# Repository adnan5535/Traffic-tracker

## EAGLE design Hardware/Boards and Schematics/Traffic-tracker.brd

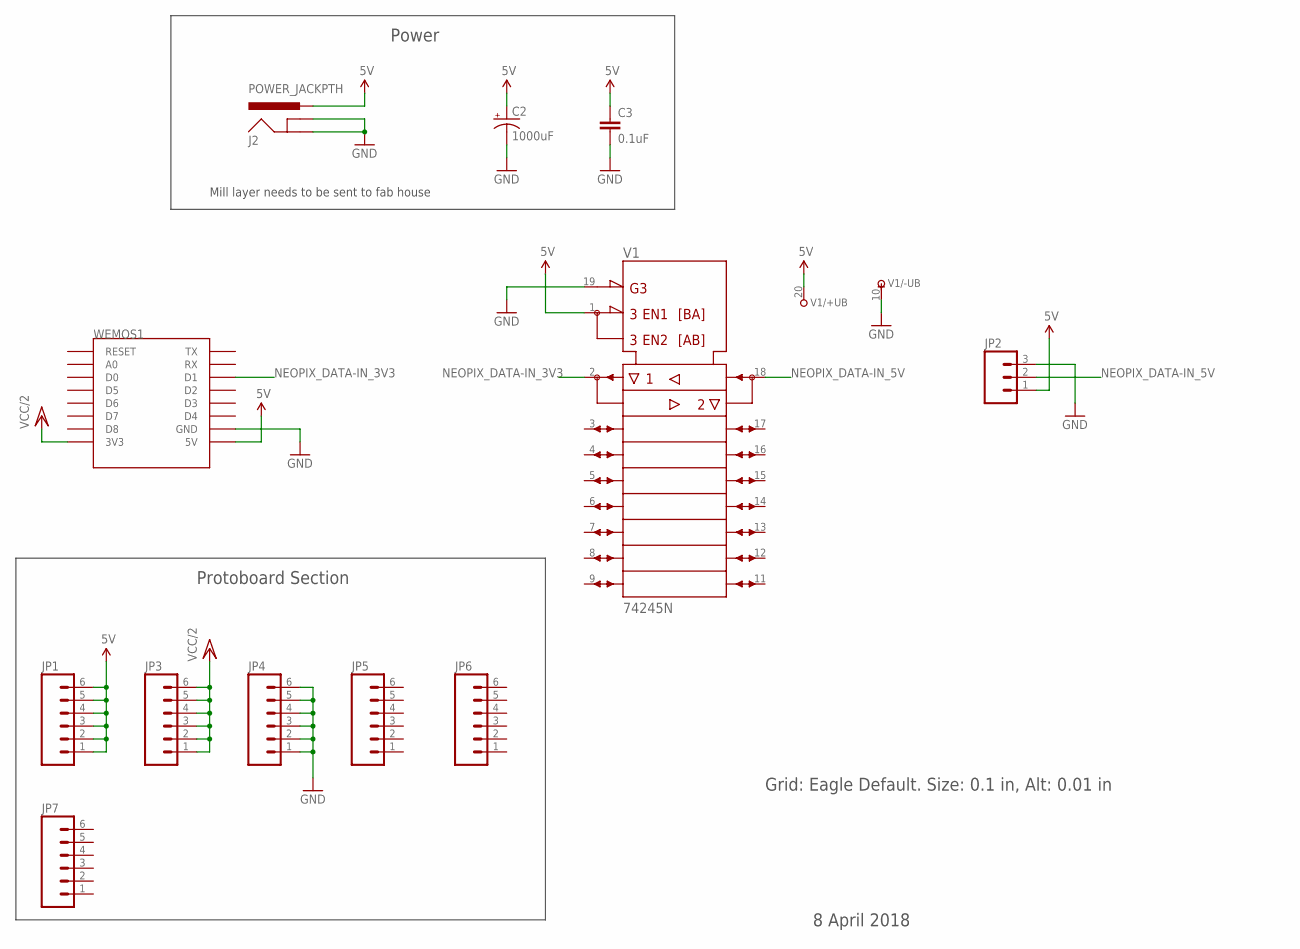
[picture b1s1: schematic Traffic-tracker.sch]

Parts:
C2: 1000uF; CPOL-RADIAL-1000UF-25V
C3: 0.1uF; 0603-CAP
J2: POWER_JACKPTH; POWER_JACK_PTH
JP1, JP3, JP4, JP5, JP6, JP7: M06POGOPIN_HOLES_ONLY; 1X06_HOLES_ONLY
JP2: M03-SCREW-5MM; SCREWTERMINAL-5MM-3
V1: 74245N; DIL20
WEMOS1: WEMOS-D1-MINI

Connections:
5V: C2.1 (+), C3.1, J2.PWR, JP1.1, JP1.2, JP1.3, JP1.4, JP1.5, JP1.6, JP2.1, V1.1 (DIR), V1.20 (+UB), WEMOS1.5V
GND: C2.2 (-), C3.2, J2.GND, J2.GNDBREAK, JP2.3, JP4.1, JP4.2, JP4.3, JP4.4, JP4.5, JP4.6, V1.10 (-UB), V1.19 (!G), WEMOS1.GND
NEOPIX_DATA-IN_3V3: V1.2 (A1), WEMOS1.D1
NEOPIX_DATA-IN_5V: JP2.2, V1.18 (B1)
VCC/2: JP3.1, JP3.2, JP3.3, JP3.4, JP3.5, JP3.6, WEMOS1.3V3

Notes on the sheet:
Mill layer needs to be sent to fab house
Power
8 April 2018
Grid: Eagle Default. Size: 0.1 in, Alt: 0.01 in
Protoboard Section

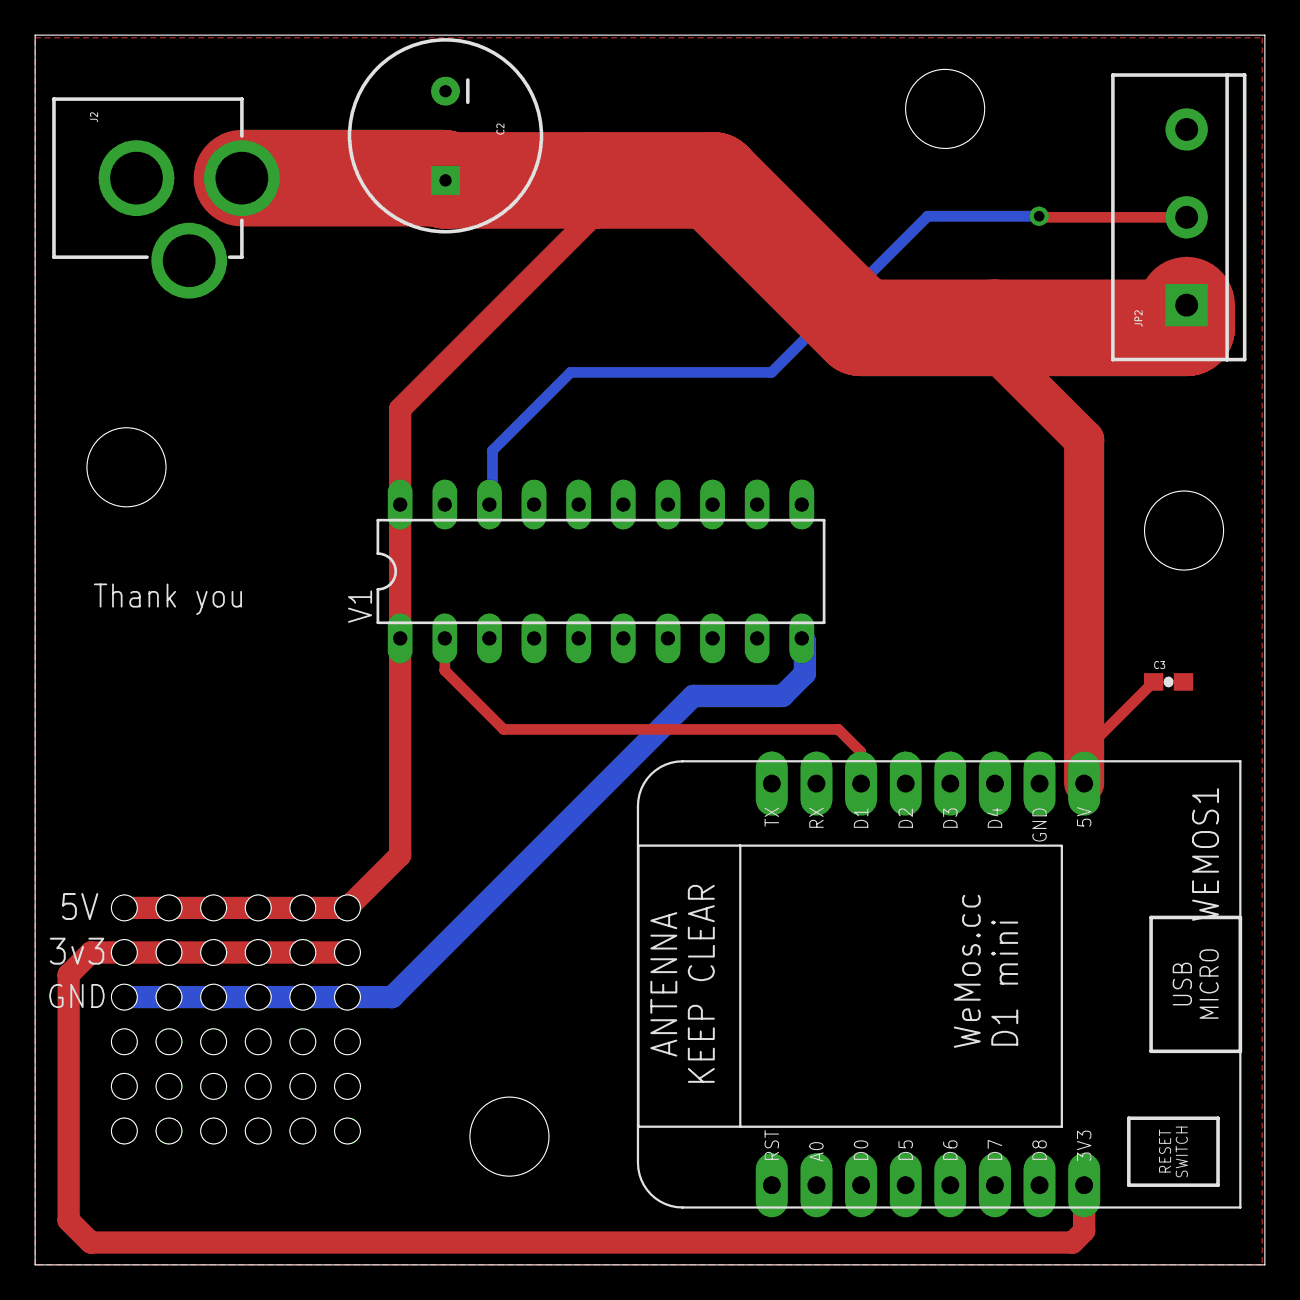
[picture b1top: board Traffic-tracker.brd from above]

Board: 2 copper layers, 70.0 x 70.0 mm, 12 parts (0 on the bottom side), 5 nets.

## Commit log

2018-04-07 Intial commit
2018-04-08 Cleaned up schematic, generated and laid out board
    Added a 2,2mm barrel jack, 3 pos jumper (for neopixel connection), and
    logic level shifter (74AHCT245). Organised schematic neatly.
    Board file generated, barrel jack connections double checked, big-ass
    trace for 4A connection to neopixels routed. Tried to keep wifi antenna
    away from big-ass power traces.
    Double checked logic level shifter connections.
2018-04-09 Added .gitignore
2018-04-09 Added protoboard section, cleaned up directory
    Protoboard section with rails for 5V, 3v3, GND, and extra holes have
    been added.
    Trying to remove autosave .brd and .sch files
2018-04-14 Added "thank you", protoboard labels, gerbers
    Thank you message added to tnames layer
    Labels for 5V, 3v3, and GND sections on protoboard
    Generated gerbers using SEEED Studio CAM file and added .zip file

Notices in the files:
parts and their libraries:
SparkFun: Licensing: CC v3.0 Share-Alike You are welcome to use this library for commercial purposes.
